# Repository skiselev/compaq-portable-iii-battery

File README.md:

# Compaq Portable III Battery Module
Battery Module for Compaq Portable III

## Introduction

Battery module replacement for the Compaq Portable III using a CR2477N coin cell battery

### Schematic and PCB Layout

[Schematic](KiCad/Compaq_Portable_III_Battery-Schematic.pdf)

[PCB Layout](KiCad/Compaq_Portable_III_Battery-Board.pdf)

### Bill of Materials

[Compaq Portable III Battery Module project on Mouser.com](https://www.mouser.com/ProjectManager/ProjectDetail.aspx?AccessID=ce89cbe21a) - View and order all components except of the PCB.
[Compaq Portable III Battery Module  on OSH Park](https://oshpark.com/shared_projects/eMKmGV3U) - View and order the PCB.

Component type    	| Reference | Description                           | Quantity | Possible sources and notes 
------------------ | --------- | -------------------------------------- | -------- | --------------------------
PCB                |           | Compaq Portable III Battery Module PCB | 1        | Order from a PCB manufacturer of your choice using provided Gerber or KiCad files
Battery Holder     | BT1       | CR2477N coin cell battery holder       | 1        | Mouser [614-SMTU2477N-LF](https://www.mouser.com/ProductDetail/614-SMTU2477N-LF)
Battery            | BT1       | CR2477N coin cell battery              | 1        | Mouser [614-CR2477N.IB](https://www.mouser.com/ProductDetail/614-CR2477N.IB)
Pin Header         | J1-J4     | 1x1 pin header                         | 4        | 

### Assembly Notes

1. Solder pin headers first:
  * Insert the pin headers from the top side of the board "upside down", with the longer ends going through the PCB
  * Flip the board so the bottom side is on the top and place on an even surface
  * Make sure that the pin headers are perpendicular to the board
  * Carefully solder the pin headers, applying the solder and the soldering iron as close to the PCB as possible, avoiding any excess of solder on the pins
2. Solder the battery holder:
  * Tin the PCB pad with a small amount of solder
  * Place the battery holder on the PCB, observing the polarity: The + marking on the battery holder should match the + marking on the PCB
  * Heat the battery holder tabs with a tinned soldering iron, the solder should appear between the tabs and the PCB
3. Insert the battery

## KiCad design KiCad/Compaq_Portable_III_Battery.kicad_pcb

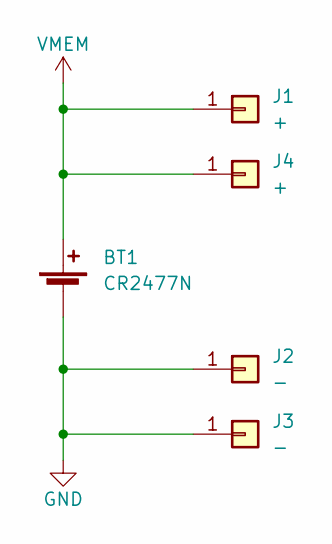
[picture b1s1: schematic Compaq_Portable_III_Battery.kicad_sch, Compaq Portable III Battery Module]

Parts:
BT1: CR2477N; Battery_Holder_Renata_SMTU2477N-LF_Hand_Soldering
J1, J4: +; Conn_Pin_Header_1x1_2.54mm
J2, J3: -; Conn_Pin_Header_1x1_2.54mm_NoKey

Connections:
GND: BT1.2 (-), J2.1, J3.1
VMEM: BT1.1 (+), J1.1, J4.1

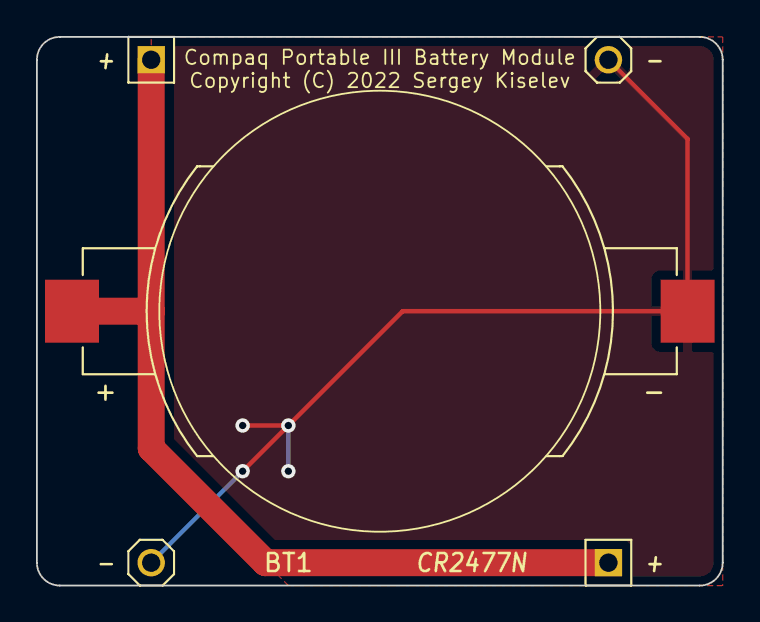
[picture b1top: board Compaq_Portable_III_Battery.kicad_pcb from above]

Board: 2 copper layers, 38.1 x 30.5 mm, 5 parts (0 on the bottom side), 2 nets.

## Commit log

2022-05-24 Add a photo

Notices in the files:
KiCad/Compaq_Portable_III_Battery.kicad_pcb:
Licensed under CERN-OHL-S: https://cern-ohl.web.cern.ch
Copyright (C) 2022 Sergey Kiselev
